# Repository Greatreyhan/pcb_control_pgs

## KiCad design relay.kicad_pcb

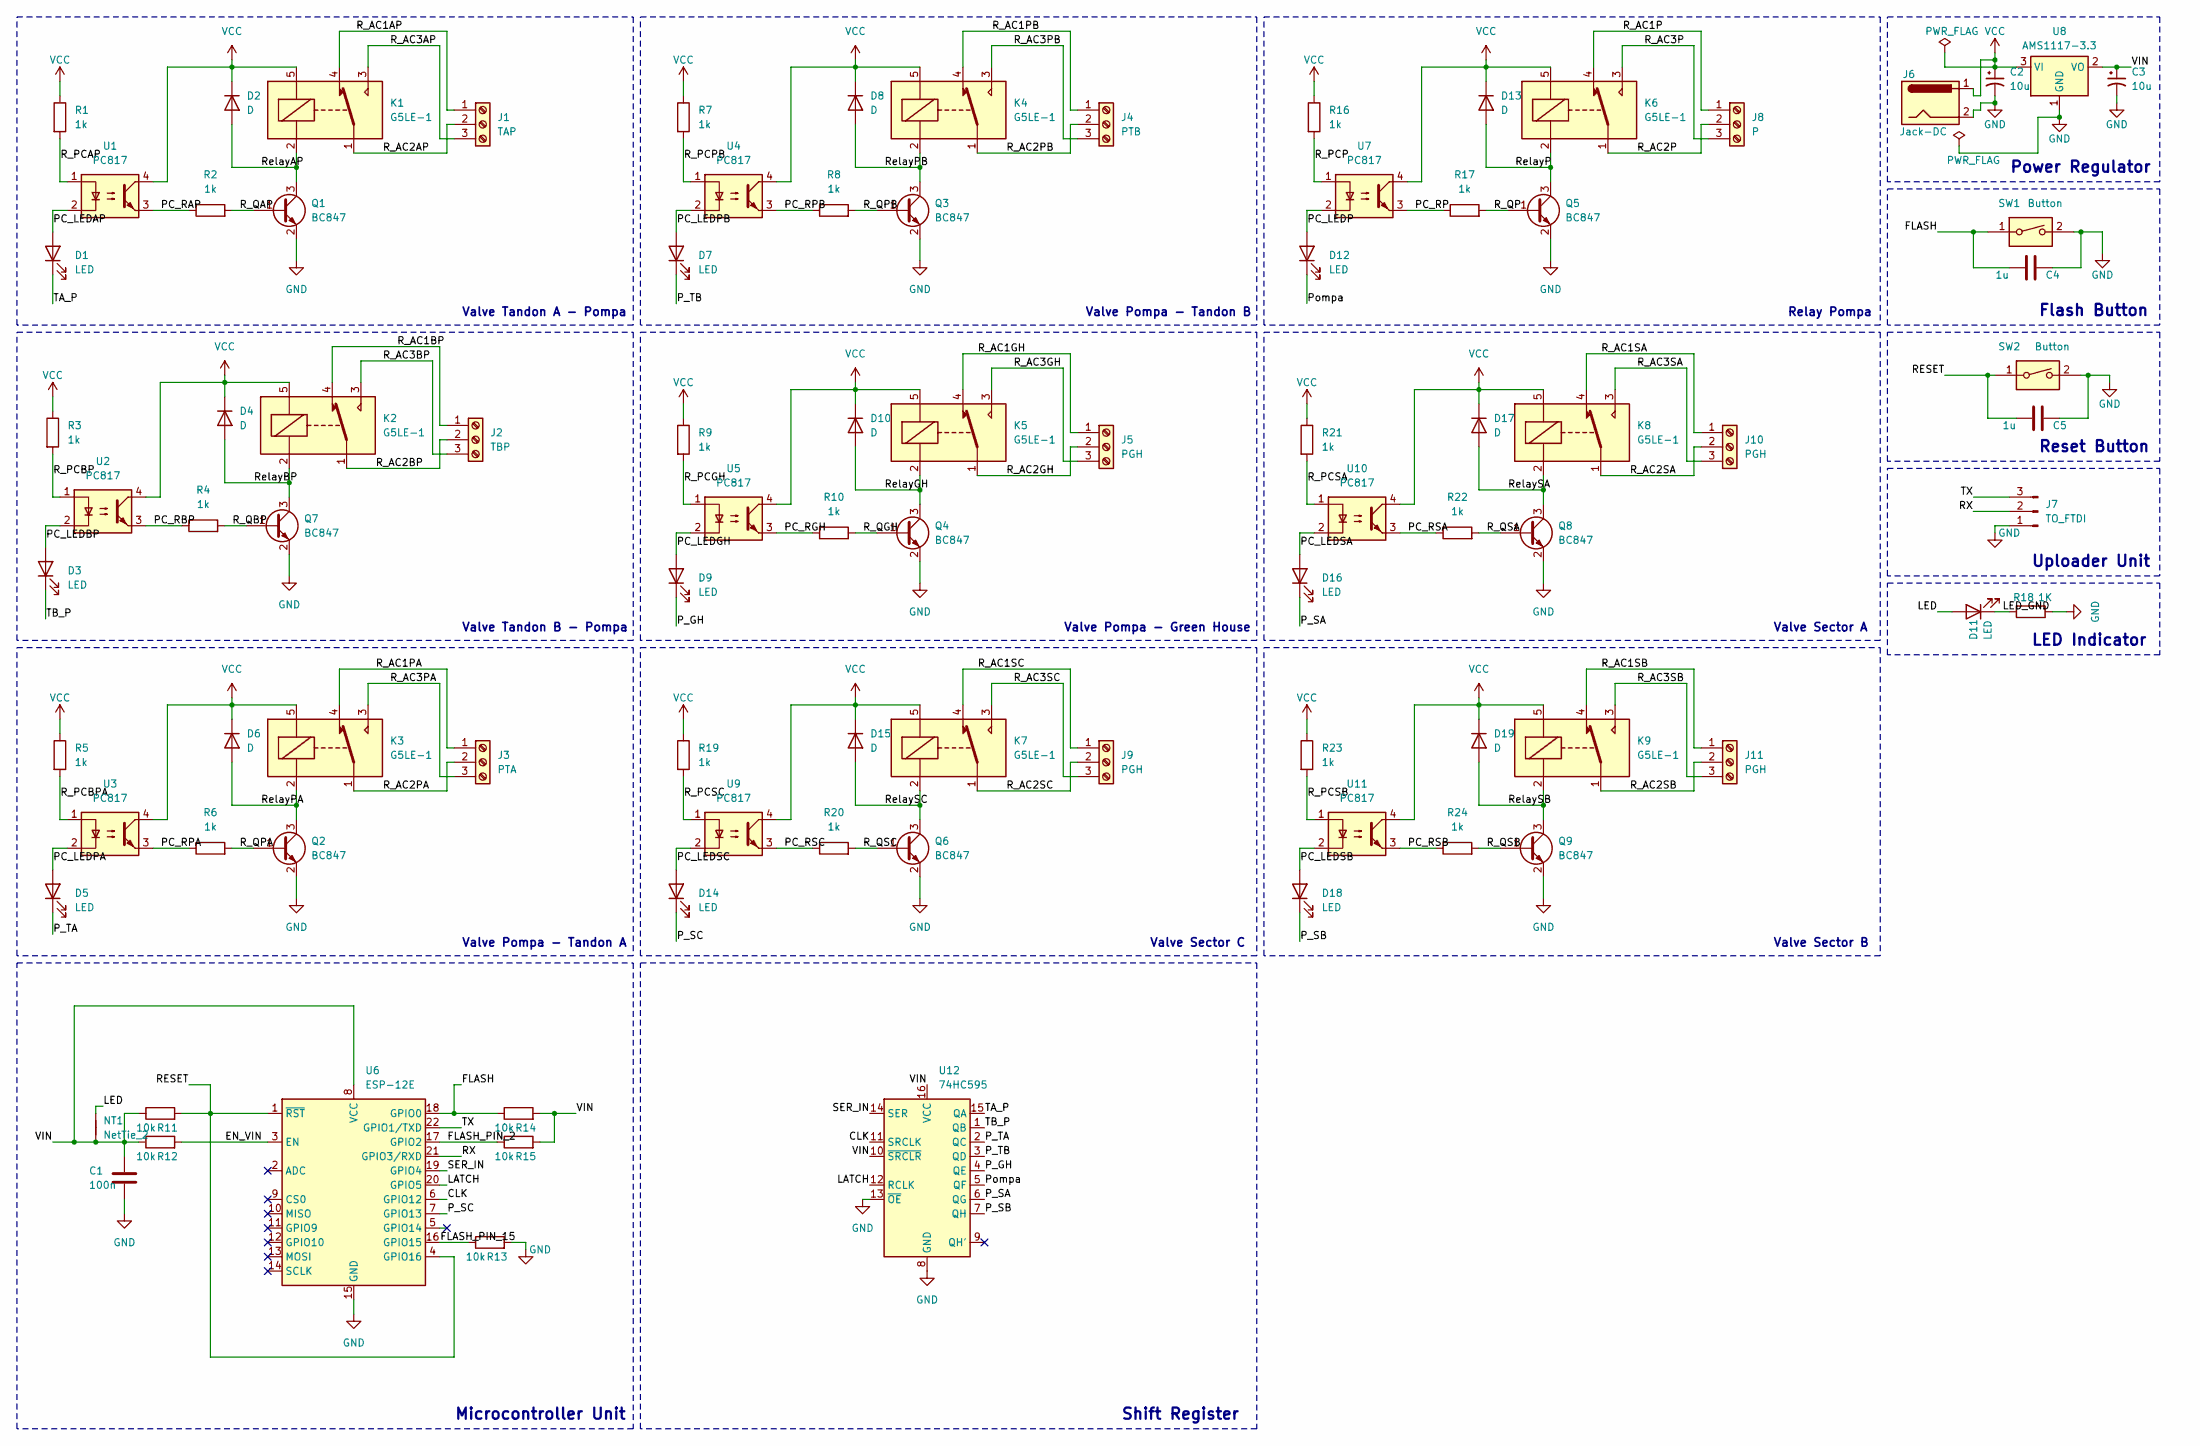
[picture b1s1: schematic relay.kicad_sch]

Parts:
C1: 100n; C_1206_3216Metric_Pad1.33x1.80mm_HandSolder
C2, C3: 10u; CP_Elec_4x5.3
C4, C5: 1u; C_1206_3216Metric_Pad1.33x1.80mm_HandSolder
D1, D3, D5, D7, D9, D11, D12, D14, D16, D18: LED; LED_1206_3216Metric_Pad1.42x1.75mm_HandSolder
D2, D4, D6, D8, D10, D13, D15, D17, D19: D; D_SMA_Handsoldering
J1: TAP; TerminalBlock_bornier-3_P5.08mm
J2: TBP; TerminalBlock_bornier-3_P5.08mm
J3: PTA; TerminalBlock_bornier-3_P5.08mm
J4: PTB; TerminalBlock_bornier-3_P5.08mm
J5, J9, J10, J11: PGH; TerminalBlock_bornier-3_P5.08mm
J6: Jack-DC; BarrelJack_SwitchcraftConxall_RAPC10U_Horizontal
J7: TO_FTDI; PinSocket_1x03_P2.54mm_Vertical
J8: P; TerminalBlock_bornier-3_P5.08mm
K1, K2, K3, K4, K5, K6, K7, K8, K9: G5LE-1; Relay_SPDT_Omron-G5LE-1
NT1: NetTie_2; NetTie-2_THT_Pad0.3mm
Q1, Q2, Q3, Q4, Q5, Q6, Q7, Q8, Q9: BC847; SOT-23
R1, R2, R3, R4, R5, R6, R7, R8, R9, R10, R16, R17, R19, R20, R21, R22, R23, R24: 1k; R_1206_3216Metric_Pad1.30x1.75mm_HandSolder
R11, R12, R13, R14, R15: 10k; R_1206_3216Metric_Pad1.30x1.75mm_HandSolder
R18: 1K; R_1206_3216Metric_Pad1.30x1.75mm_HandSolder
SW1, SW2: Button; SW_Push_1P1T_NO_CK_KSC6xxJ
U1, U2, U3, U4, U5, U7, U9, U10, U11: PC817; DIP-4_W7.62mm
U6: ESP-12E
U8: AMS1117-3.3; SOT-223-3_TabPin2
U12: 74HC595; SOIC-16_3.9x9.9mm_P1.27mm

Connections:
/CLK: U6.6 (GPIO12), U12.11 (SRCLK)
/EN_VIN: R12.2, U6.3 (EN)
/FLASH: C4.2, R14.1, SW1.1, U6.18 (GPIO0)
/FLASH_PIN_2: R15.1, U6.17 (GPIO2)
/FLASH_PIN_15: R13.1, U6.16 (GPIO15)
/LATCH: U6.20 (GPIO5), U12.12 (RCLK)
/LED: D11.2 (A), NT1.2
/LED_GND: D11.1 (K), R18.2
/PC_LEDAP: D1.2 (A), U1.2
/PC_LEDBP: D3.2 (A), U2.2
/PC_LEDGH: D9.2 (A), U5.2
/PC_LEDP: D12.2 (A), U7.2
/PC_LEDPA: D5.2 (A), U3.2
/PC_LEDPB: D7.2 (A), U4.2
/PC_LEDSA: D16.2 (A), U10.2
/PC_LEDSB: D18.2 (A), U11.2
/PC_LEDSC: D14.2 (A), U9.2
/PC_RAP: R2.1, U1.3
/PC_RBP: R4.1, U2.3
/PC_RGH: R10.1, U5.3
/PC_RP: R17.1, U7.3
/PC_RPA: R6.1, U3.3
/PC_RPB: R8.1, U4.3
/PC_RSA: R22.1, U10.3
/PC_RSB: R24.1, U11.3
/PC_RSC: R20.1, U9.3
/P_GH: D9.1 (K), U12.4 (QE)
/P_SA: D16.1 (K), U12.6 (QG)
/P_SB: D18.1 (K), U12.7 (QH)
/P_SC: D14.1 (K), U6.7 (GPIO13)
/P_TA: D5.1 (K), U12.2 (QC)
/P_TB: D7.1 (K), U12.3 (QD)
/Pompa: D12.1 (K), U12.5 (QF)
/RESET: C5.2, R11.2, SW2.1, U6.1 (~RST), U6.4 (GPIO16)
/RX: J7.2, U6.21 (GPIO3/RXD)
/R_AC1AP: J1.1, K1.4
/R_AC1BP: J2.1, K2.4
/R_AC1GH: J5.1, K5.4
/R_AC1P: J8.1, K6.4
/R_AC1PA: J3.1, K3.4
/R_AC1PB: J4.1, K4.4
/R_AC1SA: J10.1, K8.4
/R_AC1SB: J11.1, K9.4
/R_AC1SC: J9.1, K7.4
/R_AC2AP: J1.2, K1.1
/R_AC2BP: J2.2, K2.1
/R_AC2GH: J5.2, K5.1
/R_AC2P: J8.2, K6.1
/R_AC2PA: J3.2, K3.1
/R_AC2PB: J4.2, K4.1
/R_AC2SA: J10.2, K8.1
/R_AC2SB: J11.2, K9.1
/R_AC2SC: J9.2, K7.1
/R_AC3AP: J1.3, K1.3
/R_AC3BP: J2.3, K2.3
/R_AC3GH: J5.3, K5.3
/R_AC3P: J8.3, K6.3
/R_AC3PA: J3.3, K3.3
/R_AC3PB: J4.3, K4.3
/R_AC3SA: J10.3, K8.3
/R_AC3SB: J11.3, K9.3
/R_AC3SC: J9.3, K7.3
/R_PCAP: R1.2, U1.1
/R_PCBP: R3.2, U2.1
/R_PCBPA: R5.2, U3.1
/R_PCGH: R9.2, U5.1
/R_PCP: R16.2, U7.1
/R_PCPB: R7.2, U4.1
/R_PCSA: R21.2, U10.1
/R_PCSB: R23.2, U11.1
/R_PCSC: R19.2, U9.1
/R_QAP: Q1.1 (B), R2.2
/R_QBP: Q7.1 (B), R4.2
/R_QGH: Q4.1 (B), R10.2
/R_QP: Q5.1 (B), R17.2
/R_QPA: Q2.1 (B), R6.2
/R_QPB: Q3.1 (B), R8.2
/R_QSA: Q8.1 (B), R22.2
/R_QSB: Q9.1 (B), R24.2
/R_QSC: Q6.1 (B), R20.2
/RelayAP: D2.2 (A), K1.2, Q1.3 (C)
/RelayBP: D4.2 (A), K2.2, Q7.3 (C)
/RelayGH: D10.2 (A), K5.2, Q4.3 (C)
/RelayP: D13.2 (A), K6.2, Q5.3 (C)
/RelayPA: D6.2 (A), K3.2, Q2.3 (C)
/RelayPB: D8.2 (A), K4.2, Q3.3 (C)
/RelaySA: D17.2 (A), K8.2, Q8.3 (C)
/RelaySB: D19.2 (A), K9.2, Q9.3 (C)
/RelaySC: D15.2 (A), K7.2, Q6.3 (C)
/SER_IN: U6.19 (GPIO4), U12.14 (SER)
/TA_P: D1.1 (K), U12.15 (QA)
/TB_P: D3.1 (K), U12.1 (QB)
/TX: J7.3, U6.22 (GPIO1/TXD)
/VIN: C1.1, C3.1, NT1.1, R11.1, R12.1, R14.2, R15.2, U6.8 (VCC), U8.2 (VO), U12.10 (~SRCLR), U12.16 (VCC)
GND: C1.2, C2.2, C3.2, C4.1, C5.1, J6.2, J7.1, Q1.2 (E), Q2.2 (E), Q3.2 (E), Q4.2 (E), Q5.2 (E), Q6.2 (E), Q7.2 (E), Q8.2 (E), Q9.2 (E), R13.2, R18.1, SW1.2, SW2.2, U6.15 (GND), U8.1 (GND), U12.8 (GND), U12.13 (~OE)
VCC: C2.1, D2.1 (K), D4.1 (K), D6.1 (K), D8.1 (K), D10.1 (K), D13.1 (K), D15.1 (K), D17.1 (K), D19.1 (K), J6.1, K1.5, K2.5, K3.5, K4.5, K5.5, K6.5, K7.5, K8.5, K9.5, R1.1, R3.1, R5.1, R7.1, R9.1, R16.1, R19.1, R21.1, R23.1, U1.4, U2.4, U3.4, U4.4, U5.4, U7.4, U8.3 (VI), U9.4, U10.4, U11.4

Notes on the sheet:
Valve Sector C
Valve Tandon A - Pompa
Valve Pompa - Tandon A
Valve Tandon B - Pompa
Reset Button
Valve Sector A
Shift Register
Valve Sector B
Relay Pompa
Flash Button
Valve Pompa - Tandon B
Microcontroller Unit
Uploader Unit
Valve Pompa - Green House
Power Regulator
LED Indicator

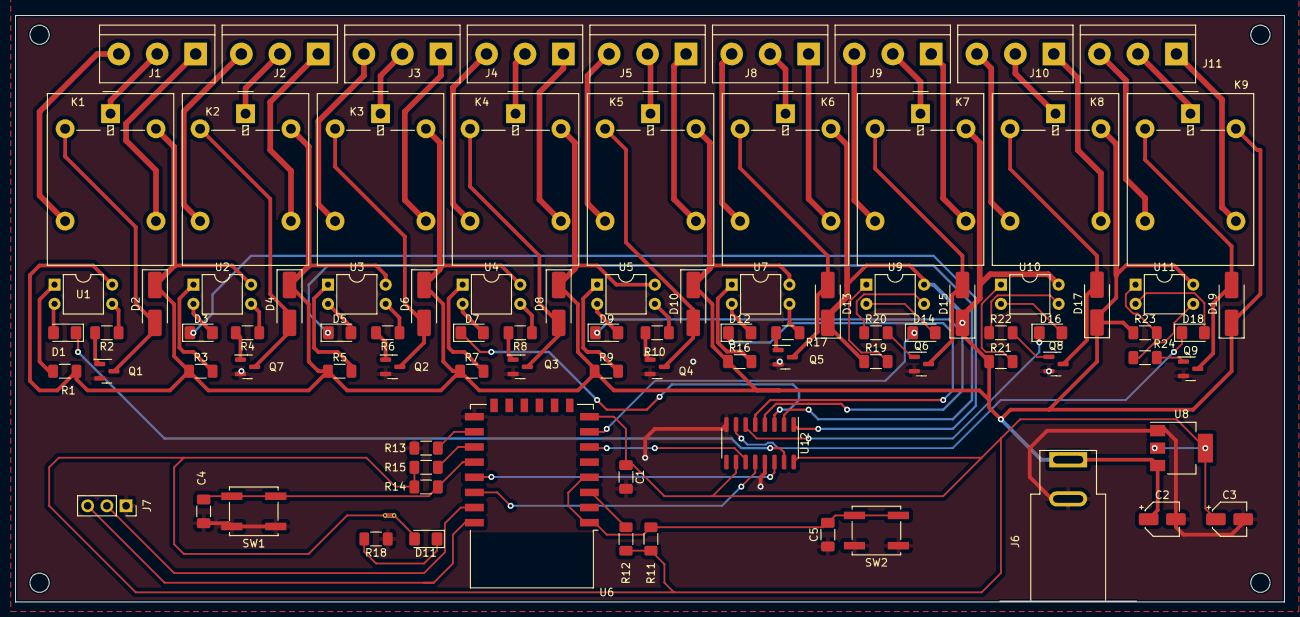
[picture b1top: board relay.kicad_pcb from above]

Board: 2 copper layers, 167.6 x 77.5 mm, 92 parts (0 on the bottom side), 96 nets.

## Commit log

2023-08-14 pcb control unrouted
2023-08-22 ready
